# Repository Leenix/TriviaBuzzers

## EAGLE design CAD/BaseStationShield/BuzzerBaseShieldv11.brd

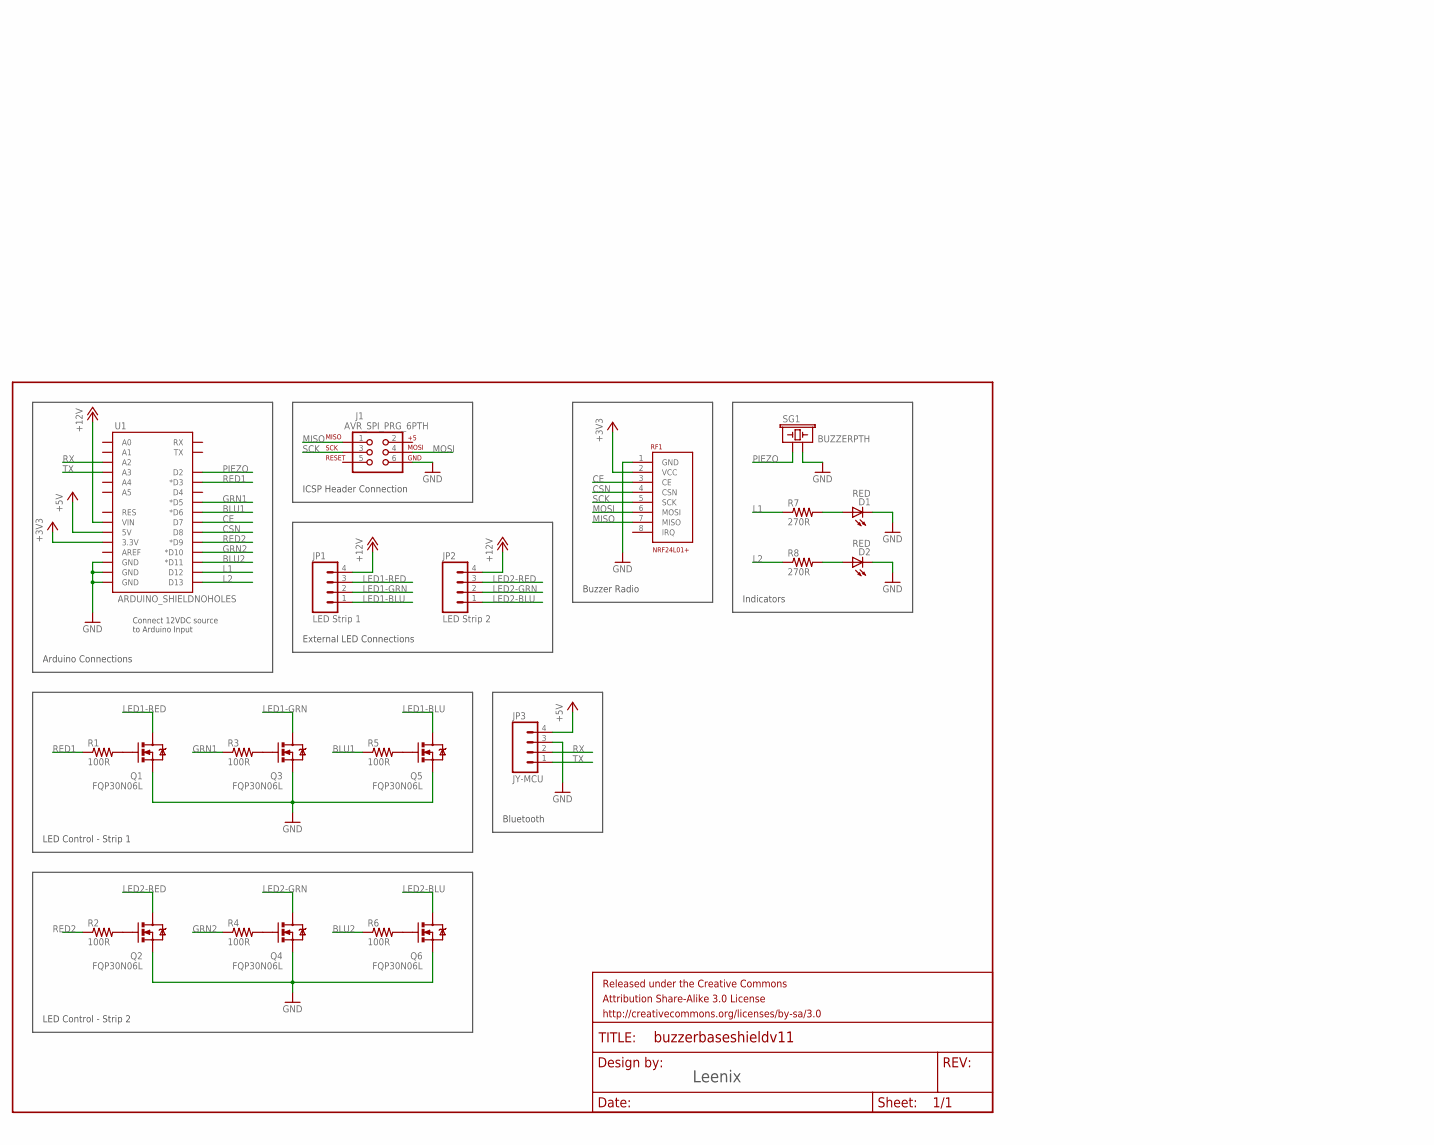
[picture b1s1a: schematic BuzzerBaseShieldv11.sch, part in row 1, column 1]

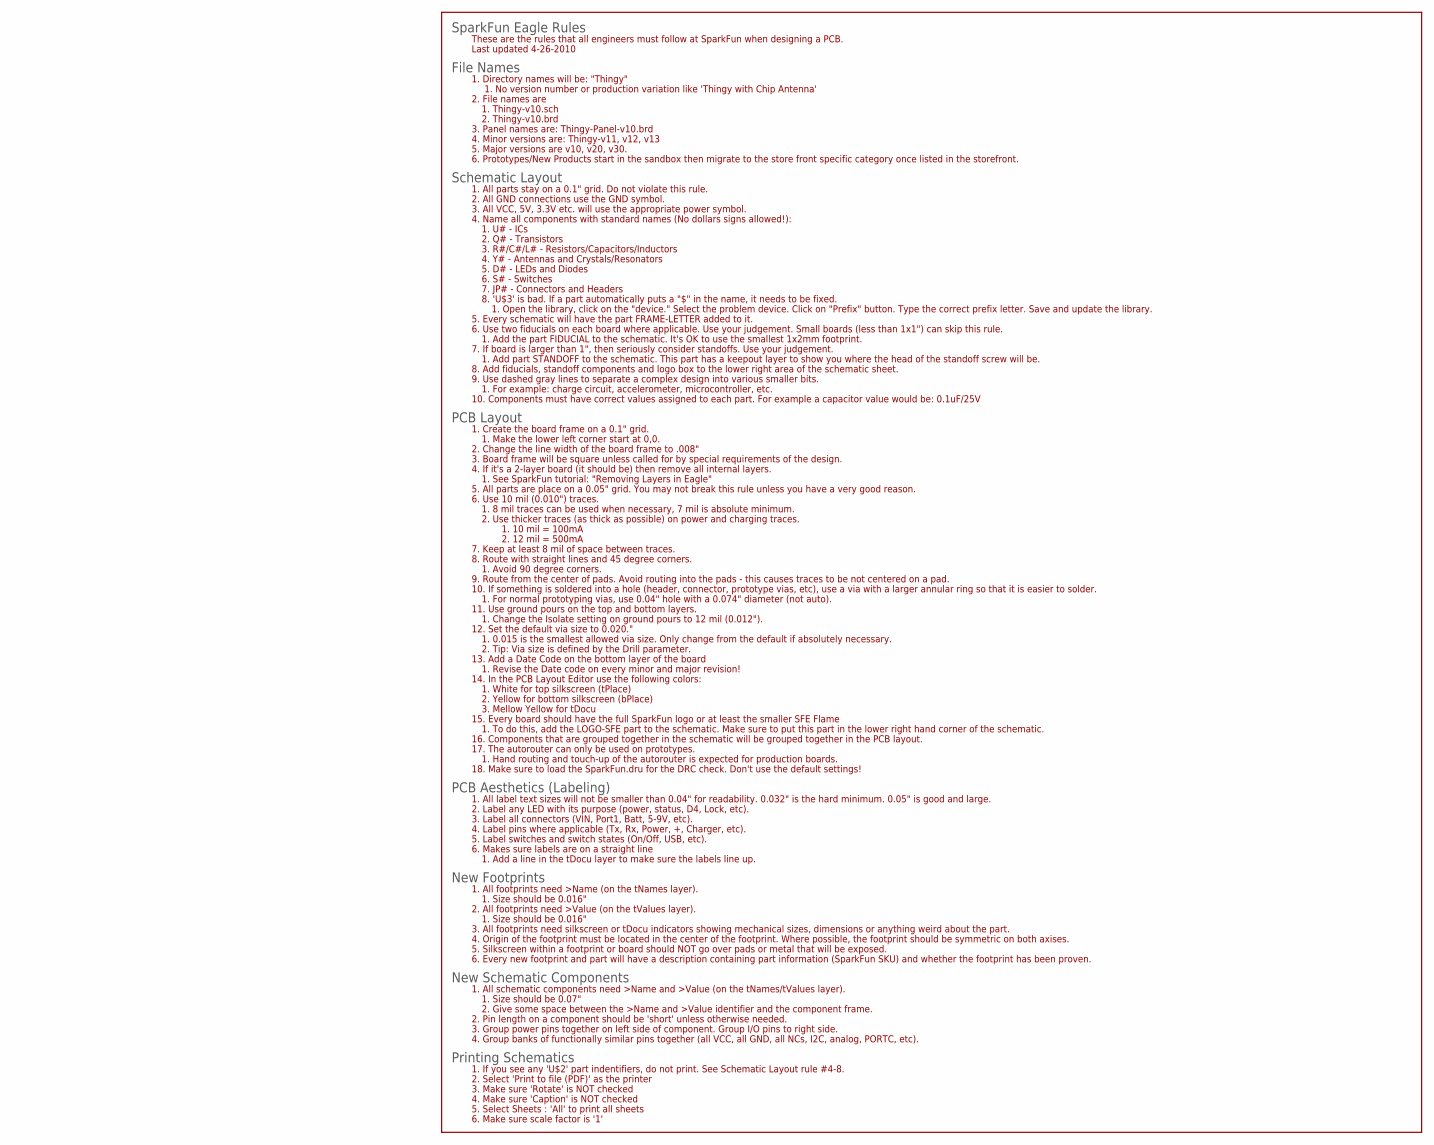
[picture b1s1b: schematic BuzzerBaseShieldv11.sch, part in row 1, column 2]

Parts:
D1, D2: RED; LED-1206
FRAME1: FRAME-LETTER; CREATIVE_COMMONS
J1: AVR_SPI_PRG_6PTH; 2X3
JP1: LED Strip 1; 1X04_LONGPADS
JP2: LED Strip 2; 1X04_LONGPADS
JP3: JY-MCU; 1X04
Q1, Q2, Q3, Q4, Q5, Q6: FQP30N06L; TO220V
R1, R2, R3, R4, R5, R6: 100R; 1206
R7, R8: 270R; 1206
RF1: NRF24L01+; NRF24L01+-HEADER
SG1: BUZZERPTH; BUZZER-12MM
U1: ARDUINO_SHIELDNOHOLES; DUEMILANOVE_SHIELD_NOHOLES

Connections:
+3V3: RF1.2 (VCC), U1.3.3V
+5V: JP3.4, U1.5V
+12V: JP1.4, JP2.4, U1.VIN
BLU1: R5.1, U1.D6 (*D6)
BLU2: R6.1, U1.D11 (*D11)
CE: RF1.3 (CE), U1.D7
CSN: RF1.4 (CSN), U1.D8
GND: D1.C, D2.C, J1.6, JP3.3, Q1.3 (S), Q2.3 (S), Q3.3 (S), Q4.3 (S), Q5.3 (S), Q6.3 (S), RF1.1 (GND), SG1.- (2), U1.GND@0 (GND), U1.GND@1 (GND), U1.GND@2 (GND)
GRN1: R3.1, U1.D5 (*D5)
GRN2: R4.1, U1.D10 (*D10)
L1: R7.1, U1.D12
L2: R8.1, U1.D13
LED1-BLU: JP1.1, Q5.2 (D)
LED1-GRN: JP1.2, Q3.2 (D)
LED1-RED: JP1.3, Q1.2 (D)
LED2-BLU: JP2.1, Q6.2 (D)
LED2-GRN: JP2.2, Q4.2 (D)
LED2-RED: JP2.3, Q2.2 (D)
MISO: J1.1, RF1.7 (MISO)
MOSI: J1.4, RF1.6 (MOSI)
unnamed: D2.A, R8.2
unnamed: D1.A, R7.2
unnamed: Q1.1 (G), R1.2
unnamed: Q5.1 (G), R5.2
unnamed: Q3.1 (G), R3.2
unnamed: Q6.1 (G), R6.2
unnamed: Q4.1 (G), R4.2
unnamed: Q2.1 (G), R2.2
PIEZO: SG1.+ (1), U1.D2
RED1: R1.1, U1.D3 (*D3)
RED2: R2.1, U1.D9 (*D9)
RX: JP3.2, U1.A2
SCK: J1.3, RF1.5 (SCK)
TX: JP3.1, U1.A3

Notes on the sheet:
LED Control - Strip 1
LED Control - Strip 2
Arduino Connections
Buzzer Radio
Indicators
ICSP Header Connection
External LED Connections
Bluetooth
Connect 12VDC source to Arduino Input
Leenix

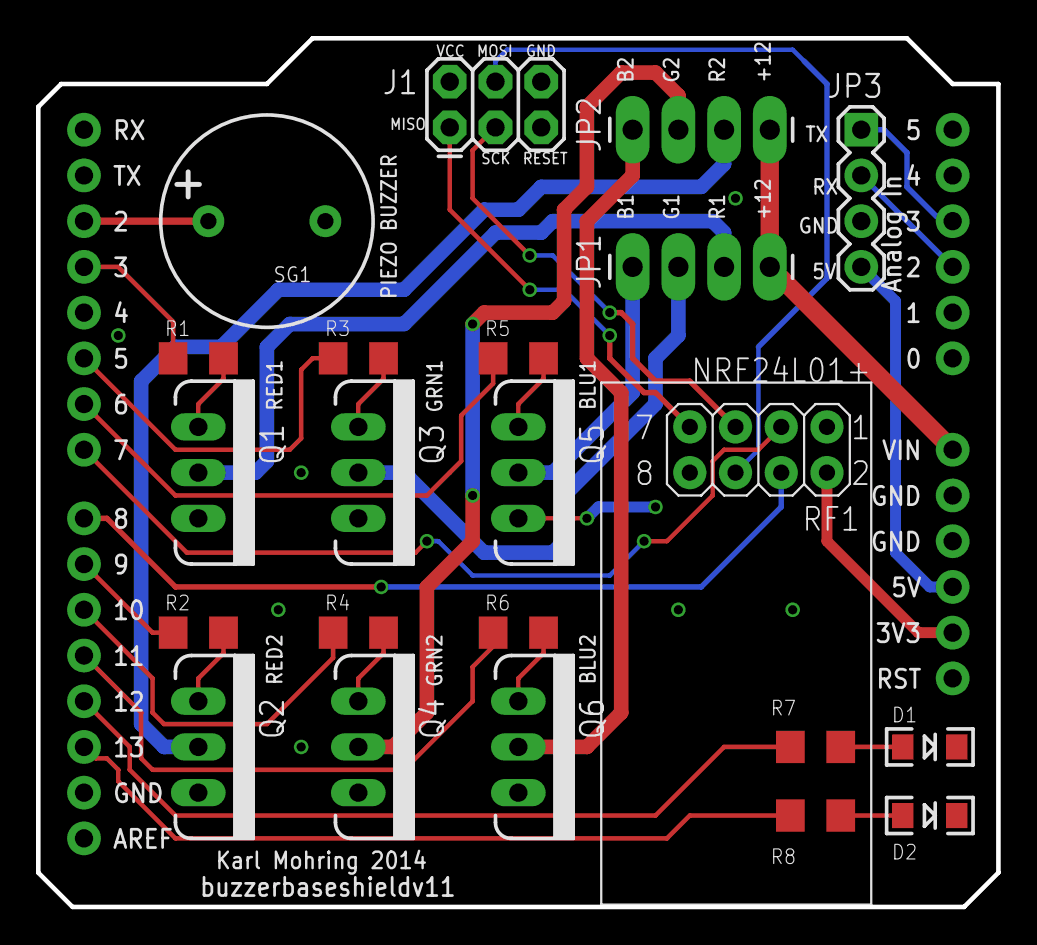
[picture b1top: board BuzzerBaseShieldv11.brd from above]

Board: 2 copper layers, 53.3 x 48.3 mm, 24 parts (0 on the bottom side), 34 nets.

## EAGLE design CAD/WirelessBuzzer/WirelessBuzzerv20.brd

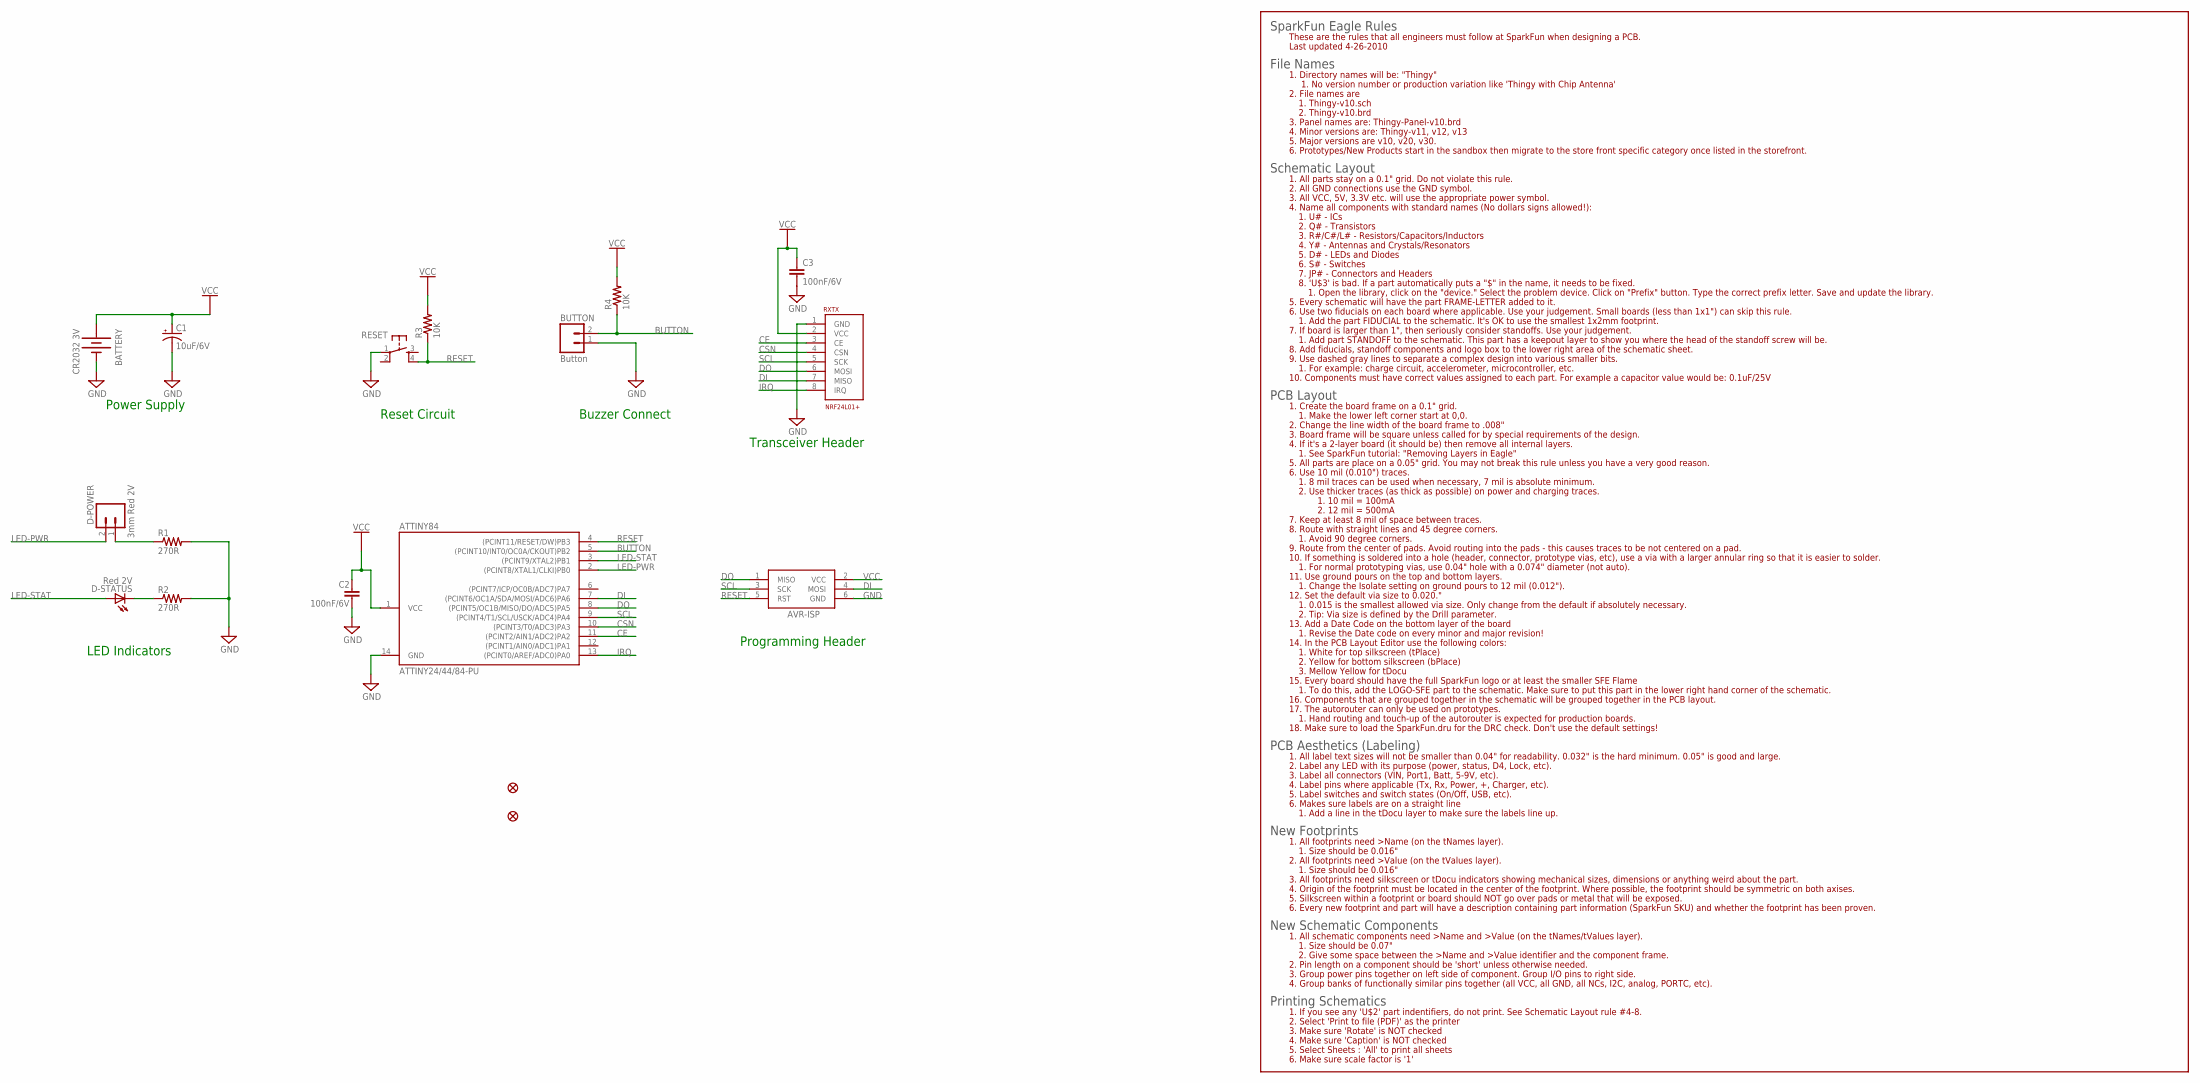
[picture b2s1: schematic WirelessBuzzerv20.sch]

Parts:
ATTINY84: ATTINY24/44/84-PU; DIL14
AVR-ISP: AVRISP-6; AVRISP
BATTERY: CR2032 3V; BATTCOM_20MM_PTH
BUTTON: Button; 1X02
C1: 10uF/6V; EIA3528-KIT
C2, C3: 100nF/6V; 1206
D-POWER: 3mm Red 2V; 1X02
D-STATUS: Red 2V; LED-1206
FID1, FID2: FIDUCIAL1.5X3; FIDUCIAL-1.5X3
R1, R2: 270R; 1206
R3, R4: 10K; 1206
RESET: DTSM-6
RXTX: NRF24L01+; NRF24L01+-HEADER

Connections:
BUTTON: ATTINY84.5 ((PCINT10/INT0/OC0A/CKOUT)PB2), BUTTON.2, R4.1
CE: ATTINY84.11 ((PCINT2/AIN1/ADC2)PA2), RXTX.3 (CE)
CSN: ATTINY84.10 ((PCINT3/T0/ADC3)PA3), RXTX.4 (CSN)
DI: ATTINY84.7 ((PCINT6/OC1A/SDA/MOSI/ADC6)PA6), AVR-ISP.4 (MOSI), RXTX.7 (MISO)
DO: ATTINY84.8 ((PCINT5/OC1B/MISO/DO/ADC5)PA5), AVR-ISP.1 (MISO), RXTX.6 (MOSI)
GND: ATTINY84.14 (GND), AVR-ISP.6 (GND), BATTERY.2 (-), BUTTON.1, C1.C (-), C2.2, C3.2, R1.2, R2.2, RESET.1, RXTX.1 (GND)
IRQ: ATTINY84.13 ((PCINT0/AREF/ADC0)PA0), RXTX.8 (IRQ)
LED-PWR: ATTINY84.2 ((PCINT8/XTAL1/CLKI)PB0), D-POWER.2
LED-STAT: ATTINY84.3 ((PCINT9/XTAL2)PB1), D-STATUS.A
unnamed: D-POWER.1, R1.1
unnamed: D-STATUS.C, R2.1
RESET: ATTINY84.4 ((PCINT11/RESET/DW)PB3), AVR-ISP.5 (RST), R3.1, RESET.4
SCL: ATTINY84.9 ((PCINT4/T1/SCL/USCK/ADC4)PA4), AVR-ISP.3 (SCK), RXTX.5 (SCK)
VCC: ATTINY84.1 (VCC), AVR-ISP.2 (VCC), BATTERY.1 (+), C1.A (+), C2.1, C3.1, R3.2, R4.2, RXTX.2 (VCC)

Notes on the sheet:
Power Supply
Reset Circuit
Buzzer Connect
Transceiver Header
LED Indicators
Programming Header

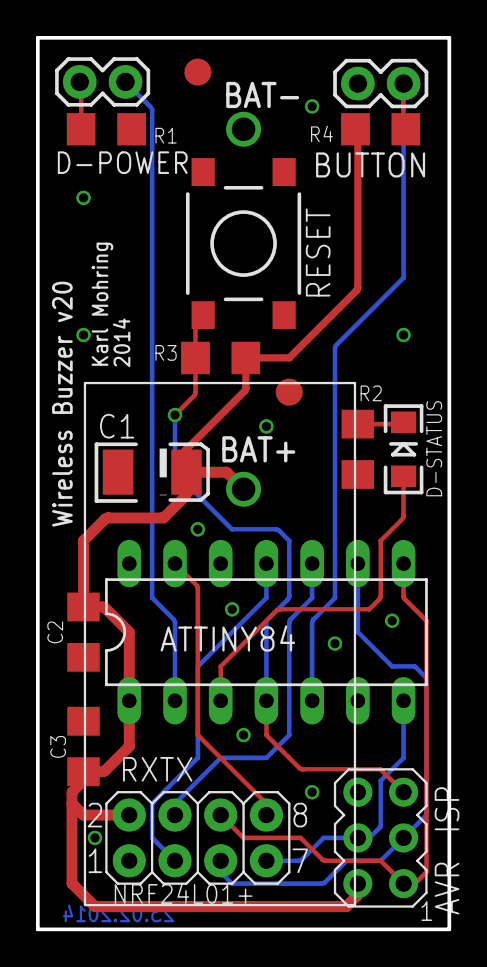
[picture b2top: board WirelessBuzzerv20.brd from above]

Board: 2 copper layers, 22.9 x 49.5 mm, 17 parts (1 on the bottom side), 14 nets.

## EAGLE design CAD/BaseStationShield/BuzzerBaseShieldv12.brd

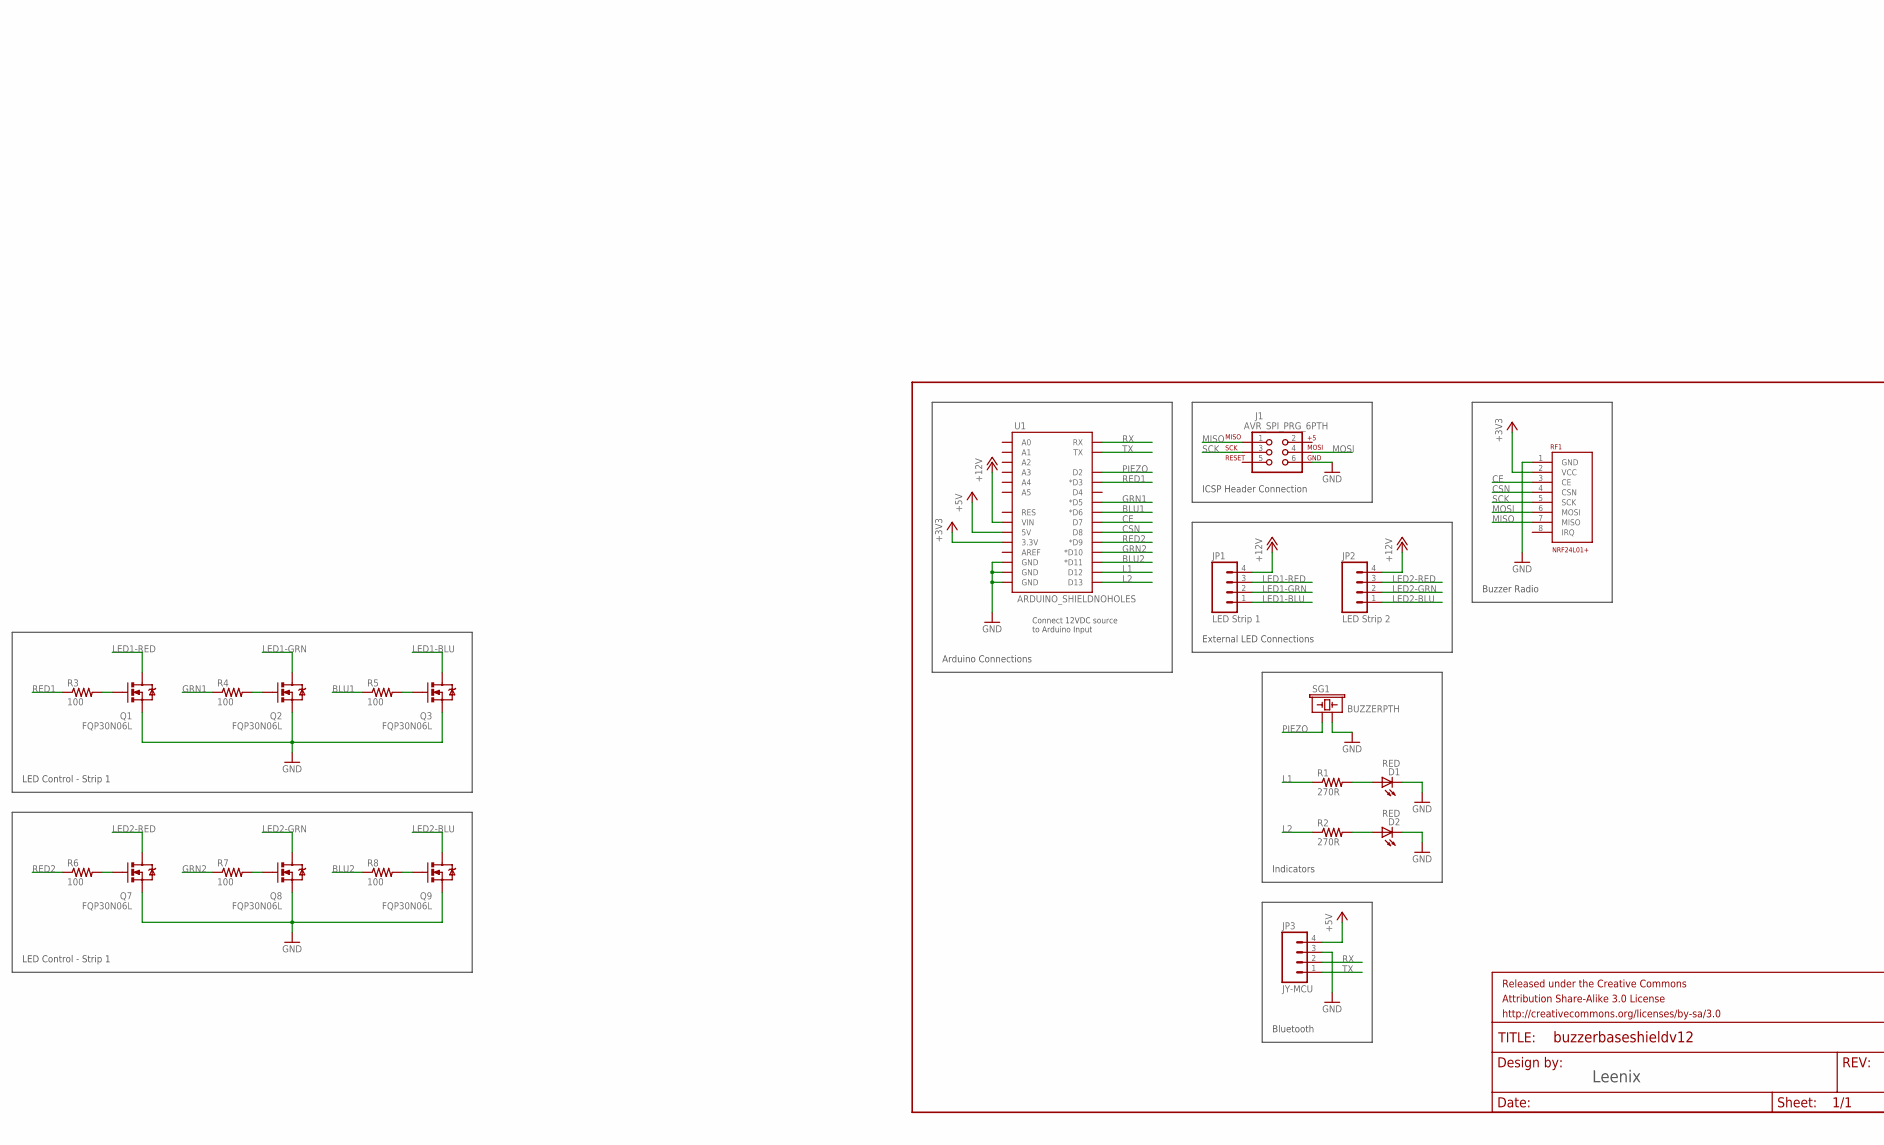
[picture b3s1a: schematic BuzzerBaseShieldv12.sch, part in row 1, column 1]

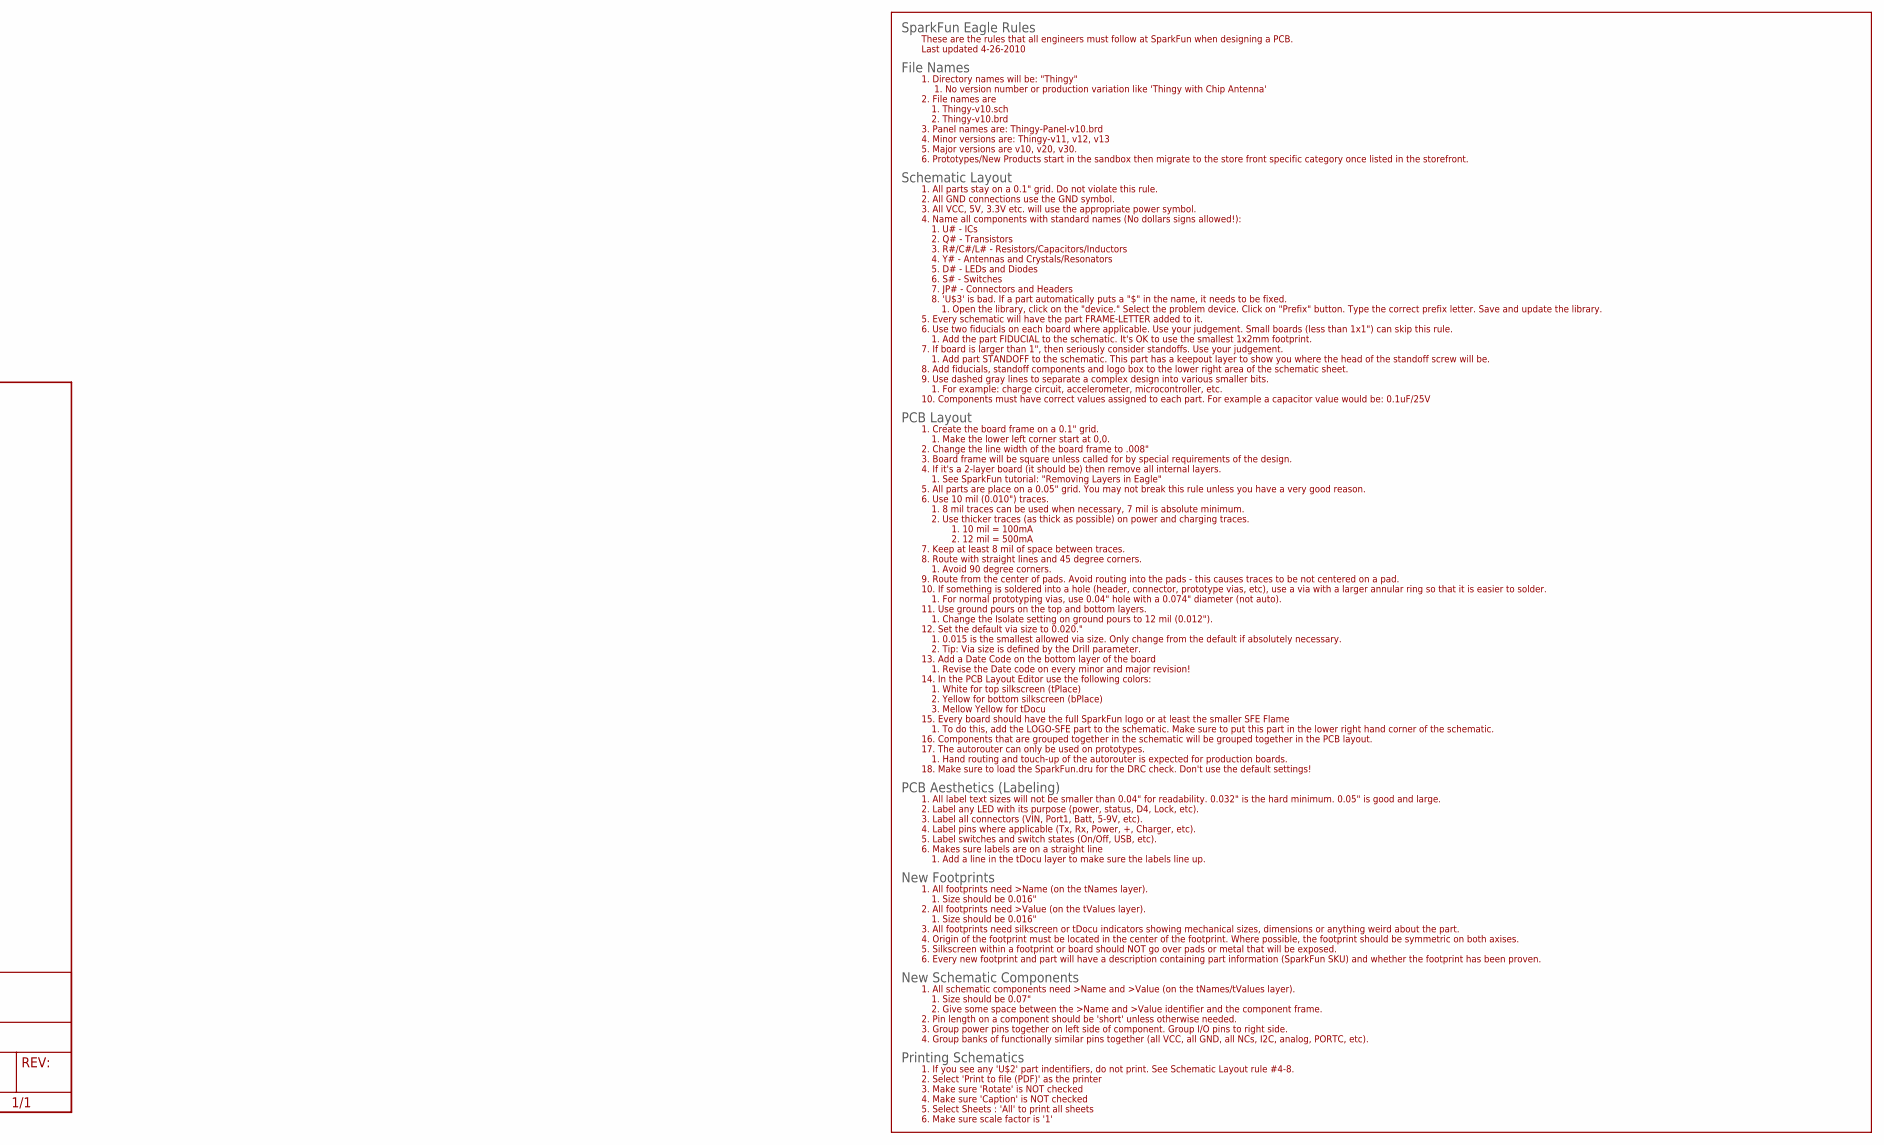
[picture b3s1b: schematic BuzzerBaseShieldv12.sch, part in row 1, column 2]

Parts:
D1, D2: RED; LED-1206
FRAME1: FRAME-LETTER; CREATIVE_COMMONS
J1: AVR_SPI_PRG_6PTH; 2X3
JP1: LED Strip 1; 1X04_LONGPADS
JP2: LED Strip 2; 1X04_LONGPADS
JP3: JY-MCU; 1X04_LONGPADS
Q1, Q2, Q3, Q7, Q8, Q9: FQP30N06L; TO220V
R1, R2: 270R; 1206
R3, R4, R5, R6, R7, R8: 100; 1206
RF1: NRF24L01+; NRF24L01+-HEADER
SG1: BUZZERPTH; BUZZER-12MM
U1: ARDUINO_SHIELDNOHOLES; DUEMILANOVE_SHIELD_NOHOLES

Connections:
+3V3: RF1.2 (VCC), U1.3.3V
+5V: JP3.4, U1.5V
+12V: JP1.4, JP2.4, U1.VIN
BLU1: R5.1, U1.D6 (*D6)
BLU2: R8.1, U1.D11 (*D11)
CE: RF1.3 (CE), U1.D7
CSN: RF1.4 (CSN), U1.D8
GND: D1.C, D2.C, J1.6, JP3.3, Q1.3 (S), Q2.3 (S), Q3.3 (S), Q7.3 (S), Q8.3 (S), Q9.3 (S), RF1.1 (GND), SG1.- (2), U1.GND@0 (GND), U1.GND@1 (GND), U1.GND@2 (GND)
GRN1: R4.1, U1.D5 (*D5)
GRN2: R7.1, U1.D10 (*D10)
L1: R1.1, U1.D12
L2: R2.1, U1.D13
LED1-BLU: JP1.1, Q3.2 (D)
LED1-GRN: JP1.2, Q2.2 (D)
LED1-RED: JP1.3, Q1.2 (D)
LED2-BLU: JP2.1, Q9.2 (D)
LED2-GRN: JP2.2, Q8.2 (D)
LED2-RED: JP2.3, Q7.2 (D)
MISO: J1.1, RF1.7 (MISO)
MOSI: J1.4, RF1.6 (MOSI)
unnamed: D2.A, R2.2
unnamed: D1.A, R1.2
unnamed: Q1.1 (G), R3.2
unnamed: Q2.1 (G), R4.2
unnamed: Q3.1 (G), R5.2
unnamed: Q7.1 (G), R6.2
unnamed: Q8.1 (G), R7.2
unnamed: Q9.1 (G), R8.2
PIEZO: SG1.+ (1), U1.D2
RED1: R3.1, U1.D3 (*D3)
RED2: R6.1, U1.D9 (*D9)
RX: JP3.2, U1.RX
SCK: J1.3, RF1.5 (SCK)
TX: JP3.1, U1.TX

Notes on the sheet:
LED Control - Strip 1
Arduino Connections
Buzzer Radio
Indicators
ICSP Header Connection
External LED Connections
Bluetooth
Connect 12VDC source to Arduino Input
Leenix

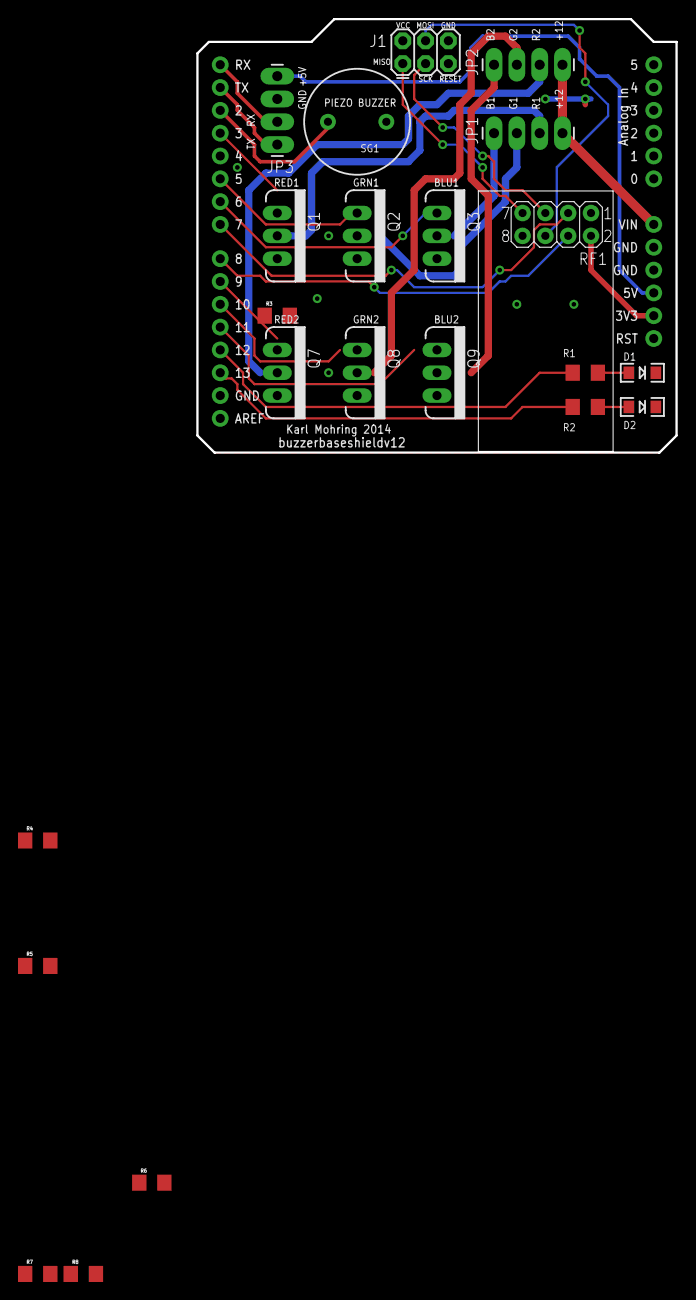
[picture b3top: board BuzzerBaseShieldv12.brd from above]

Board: 2 copper layers, 53.3 x 48.3 mm, 24 parts (0 on the bottom side), 34 nets.

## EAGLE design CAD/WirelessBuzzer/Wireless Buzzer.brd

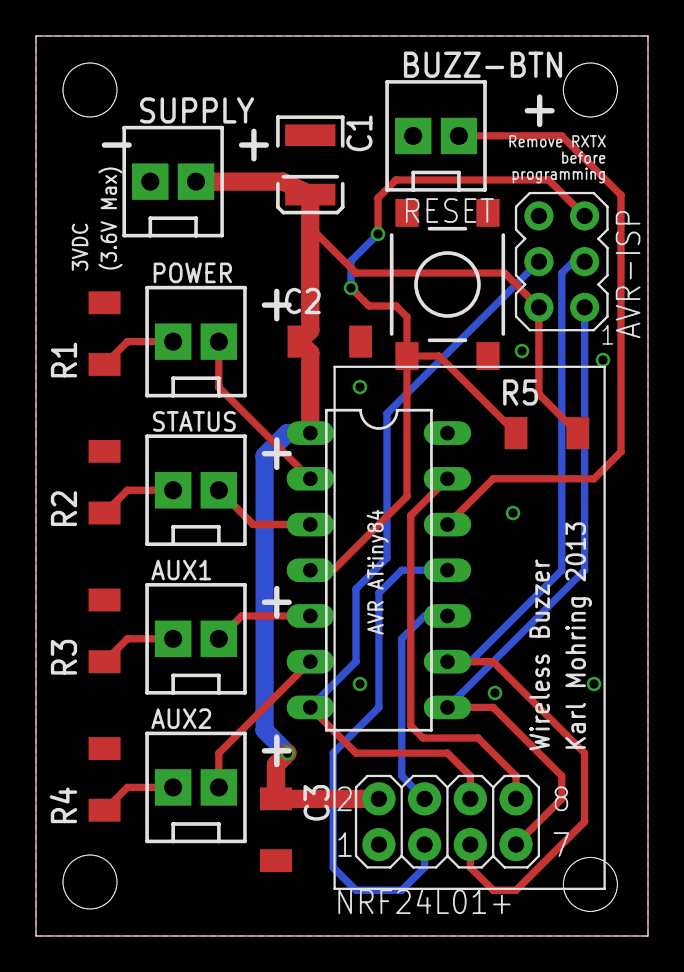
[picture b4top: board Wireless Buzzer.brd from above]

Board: 2 copper layers, 34.0 x 50.0 mm, 18 parts (0 on the bottom side), 18 nets.

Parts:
AUX1: LED 3; KK-CONNECT-2WAY-PG
AUX2: LED 4; KK-CONNECT-2WAY-PG
AVR-ISP: AVRISP
BUZZ-BTN: Button; KK-CONNECT-2WAY-PG
C1: 10uF; SM-TANT-B_EIA3528
C2, C3: 100nF; SM-1206_PG
IC1: ATTINY24/44/84-PU; DIL14
POWER: LED 1; KK-CONNECT-2WAY-PG
R1, R2, R3, R4: 270R; SM-1206_PG
R5: 10K; SM-1206_PG
RESET: DTSM-6
RXTX: NRF24L01+; NRF24L01+-HEADER
STATUS: LED 2; KK-CONNECT-2WAY-PG
SUPPLY: +3VDC; KK-CONNECT-2WAY-PG

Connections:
BUTTON: BUZZ-BTN.2, IC1.12
CE: IC1.11, RXTX.3
CS: IC1.10, RXTX.4
GND: AVR-ISP.6, BUZZ-BTN.1, C1.C, C2.P$2, C3.P$2, IC1.14, R1.P$2, R2.P$2, R3.P$2, R4.P$2, RESET.1, RXTX.1, SUPPLY.1
IRQ: IC1.13, RXTX.8
LED1: IC1.2, POWER.2
LED2: IC1.3, STATUS.2
LED3: AUX1.2, IC1.5
LED4: AUX2.2, IC1.6
MISO: AVR-ISP.1, IC1.8, RXTX.7
MOSI: AVR-ISP.4, IC1.7, RXTX.6
unnamed: POWER.1, R1.P$1
unnamed: R2.P$1, STATUS.1
unnamed: AUX1.1, R3.P$1
unnamed: AUX2.1, R4.P$1
RESET: AVR-ISP.5, IC1.4, R5.P$1, RESET.4
SCL: AVR-ISP.3, IC1.9, RXTX.5
VCC: AVR-ISP.2, C1.A, C2.P$1, C3.P$1, IC1.1, R5.P$2, RXTX.2, SUPPLY.2

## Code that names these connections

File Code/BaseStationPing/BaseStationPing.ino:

#include <SPI.h>
#include <nRF24L01.h>
#include <RF24.h>

#define CE_PIN   9
#define CSN_PIN 10

#define PIEZO 2
#define RED1_PIN 3
#define GRN1_PIN 5
#define BLU1_PIN 6

#define RED2_PIN 9
#define GRN2_PIN 10
#define BLU2_PIN 11

#define LED1_PIN 12
#define LED2_PIN 13

const uint64_t pipe = 0xE8E8F0F000LL;
const char pipeIDs[] = {'y', 'g'};

RF24 radio(CE_PIN, CSN_PIN);

char payload[1];

void setup()
{
	
}


void loop()
{
		
}

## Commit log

2015-01-27 :tada: Added .gitattributes & .gitignore files
2015-01-27 Initial commit of a really old project

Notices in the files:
parts and their libraries:
SparkFun-Aesthetics: Licensing: CC v3.0 Share-Alike You are welcome to use this library for commercial purposes.
SparkFun-Aesthetics: Released under the Creative Commons Attribution Share-Alike 3.0 License
SparkFun-Aesthetics: http://creativecommons.org/licenses/by-sa/3.0
